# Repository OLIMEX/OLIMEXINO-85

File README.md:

This is the official repository for a number of OLIMEXINO-85 boards, manufactured by Olimex.

OLIMEXINO-85 boards are very tiny Arduino-like boards. They have functionality similar to Digistump's Digispark and Adafruit’s Trinket. The ATtiny85 microcontroller of each board comes preprogrammed with "Micronucleus" bootloater. This bootloader allows you to upload new software to the board via a personal computer and a USB cable. The boards work with the same Arduino distribution as Digispark.

In this repository you would find files suitable for the following boards:  

* OLIMEXINO-85-ASM: https://www.olimex.com/Products/Duino/AVR/OLIMEXINO-85-ASM/open-source-hardware
* OLIMEXINO-85-KIT: https://www.olimex.com/Products/Soldering-Kits/OLIMEXINO-85-KIT/open-source-hardware
* OLIMEXINO-85BC: https://www.olimex.com/Products/Duino/AVR/OLIMEXINO-85BC/open-source-hardware
* OLIMEXINO-85S: https://www.olimex.com/Products/Duino/AVR/OLIMEXINO-85S/open-source-hardware
* FOSDEM-85: https://www.olimex.com/Products/Soldering-Kits/FOSDEM-85/open-source-hardware

The SIMON-85 and SIMON-85-KIT boards have own repository available here: https://github.com/OLIMEX/SIMON-85

This repository contains a number of software files - firmware binaries, Arduino libraries, and ready-to-use examples. Note that the software files for the mentioned boards are the same for all boards in this repository. However, the hardware source files and pdfs for the above-mentioned boards are not the same.

##LICENSE
* Software License is GPL3
* Hardware License is Apache 2.0
* Documentation License is CC-BY-SA3.0 (https://creativecommons.org/licenses/by-sa/3.0/)

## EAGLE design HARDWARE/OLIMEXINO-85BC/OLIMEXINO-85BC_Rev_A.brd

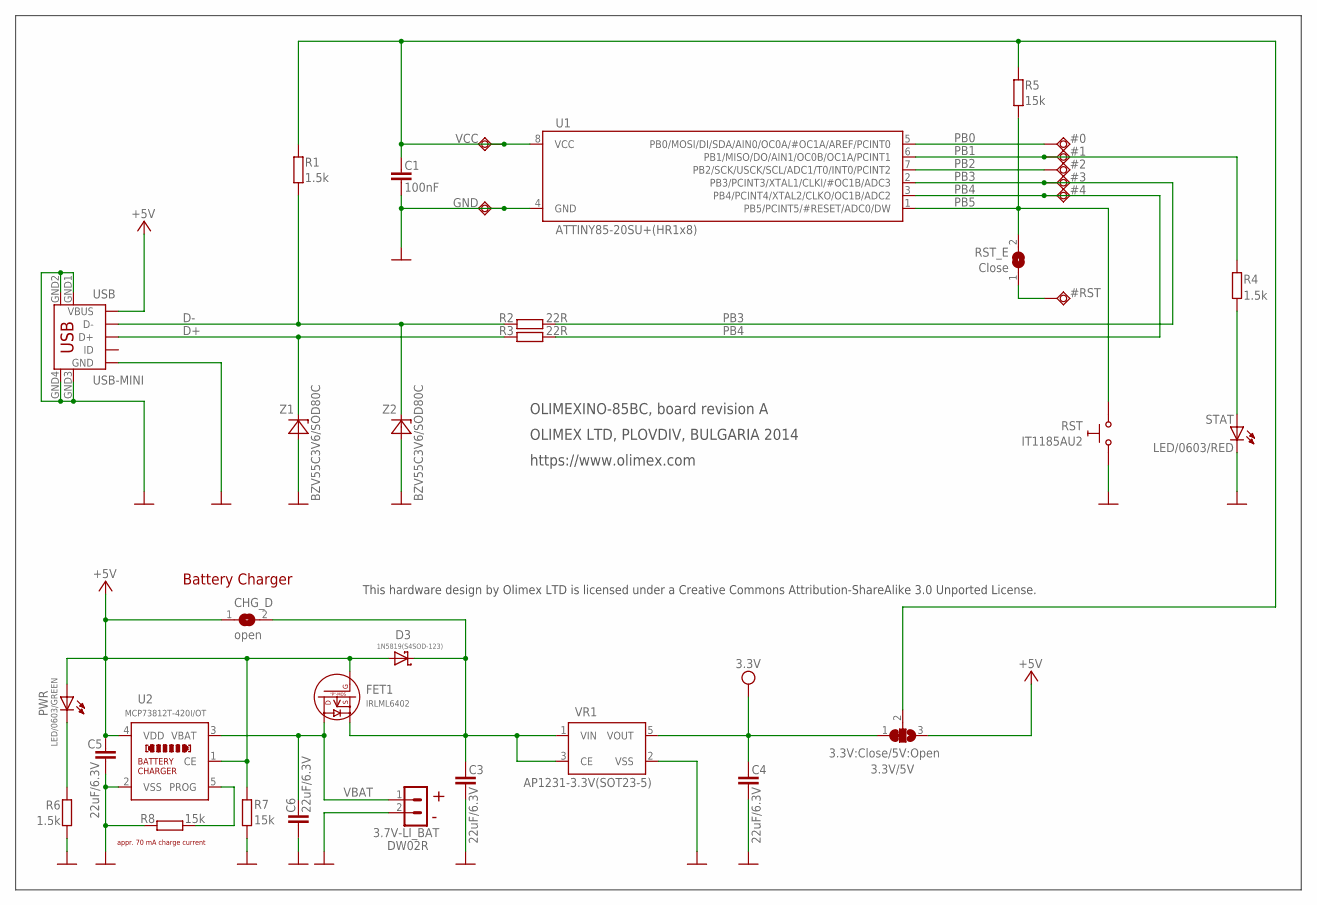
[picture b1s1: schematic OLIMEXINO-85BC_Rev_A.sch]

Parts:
3.3V/5V: 3.3V:Close/5V:Open; SJ_2_SMALL
3.7V-LI_BAT: DW02R
#0, #1, #2, #3, #4: TESTPAD3; TEST_PAD40/70/SQUARE
#RST: TESTPAD3; TEST_PAD40/70/SQUARE
C1: 100nF; C0603_DWS
C3, C4, C5, C6: 22uF/6.3V; C0603_DWS
CHG_D: open; SJ_1_SMALLER
D3: 1N5819(S4SOD-123); SOD-123
FET1: IRLML6402; SOT23
GND: TESTPAD3; TEST_PAD40/70/SQUARE
PWR: LED/0603/GREEN; LED-0603
R1, R4, R6: 1.5k; R0603_5MIL_DWS
R2, R3: 22R; R0603_5MIL_DWS
R5, R7, R8: 15k; R0603_5MIL_DWS
RST: IT1185AU2
RST_E: Close; SJ_1_SMALLER
STAT: LED/0603/RED; LED-0603
U1: ATTINY85-20SU+(HR1x8); SO-8
U2: MCP73812T-420I/OT; SOT-23-5
USB: USB-MINI; USB_MINI_9PIN
VCC: TESTPAD3; TEST_PAD40/70/SQUARE
VR1: AP1231-3.3V(SOT23-5); SOT-23-5
Z1, Z2: BZV55C3V6/SOD80C; MINI-MELF

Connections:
+5V: 3.3V/5V.3, C5.1, CHG_D.1, D3.A, FET1.1 (G), PWR.A, R7.1, U2.1 (CE), U2.4 (VDD), USB.VBUS
D+: R3.1, USB.D+, Z1.1 (C)
D-: R1.1, R2.1, USB.D-, Z2.1 (C)
GND: 3.7V-LI_BAT.2, C1.2, C3.2, C4.2, C5.2, C6.2, GND.P$1, R6.2, R7.2, R8.1, RST.2 (1), STAT.C, U1.4 (GND), U2.2 (VSS), USB.GND, USB.GND1, USB.GND2, USB.GND3, USB.GND4, VR1.2 (VSS), Z1.2 (A), Z2.2 (A)
MCU_VCC: 3.3V/5V.2, C1.1, R1.2, R5.2, U1.8 (VCC), VCC.P$1
unnamed: #RST.P$1, RST_E.1
unnamed: R4.1, STAT.A
unnamed: PWR.C, R6.1
unnamed: R8.2, U2.5 (PROG)
PB0: #0.P$1, U1.5 (PB0/MOSI/DI/SDA/AIN0/OC0A/#OC1A/AREF/PC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)
PB1: #1.P$1, R4.2, U1.6 (PB1/MISO/DO/AIN1/OC0B/OC1A/PCINT1)
PB2: #2.P$1, U1.7 (PB2/SCK/USCK/SCL/ADC1/T0/INT0/PCINT2)
PB3: #3.P$1, R2.2, U1.2 (PB3/PCINT3/XTAL1/CLKI/#OC1B/ADC3)
PB4: #4.P$1, R3.2, U1.3 (PB4/PCINT4/XTAL2/CLKO/OC1B/ADC2)
PB5: R5.1, RST.1 (0), RST_E.2, U1.1 (PB5/PCINT5/#RESET/ADC0/DW)
VBAT: 3.7V-LI_BAT.1, C6.1, FET1.3 (D), U2.3 (VBAT)
VCC: 3.3V/5V.1, C4.1, VR1.5 (VOUT)
VIN: C3.1, CHG_D.2, D3.C, FET1.2 (S), VR1.1 (VIN), VR1.3 (CE)

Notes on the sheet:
Battery Charger
appr. 70 mA charge current
OLIMEXINO-85BC, board revision A
OLIMEX LTD, PLOVDIV, BULGARIA 2014
https://www.olimex.com
This hardware design by Olimex LTD is licensed under a Creative Commons Attribution-ShareAlike 3.0 Unported License.

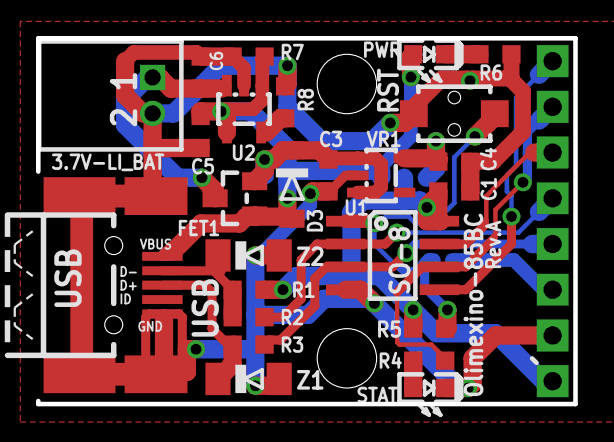
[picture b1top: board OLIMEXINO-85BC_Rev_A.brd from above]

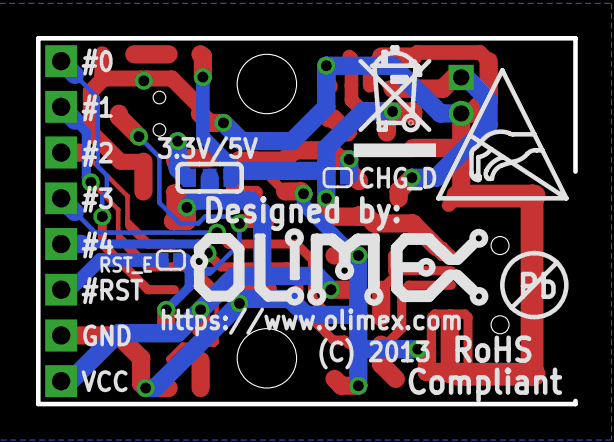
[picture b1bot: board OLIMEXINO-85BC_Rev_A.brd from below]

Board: 2 copper layers, 29.8 x 20.3 mm, 40 parts (7 on the bottom side), 18 nets.

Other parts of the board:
U$1: RECYCLE_BIN1/8
U$2: OLIMEX1_V
U$3: ESD_SYMBOL
U$4: PB_SMALL

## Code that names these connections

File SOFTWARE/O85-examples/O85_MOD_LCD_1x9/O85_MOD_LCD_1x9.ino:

/**********************************************************************************/
/*    Demo Program for:          						  */
/*	  Board: Olimexino-85                 					  */
/*    Manufacture: OLIMEX                                                   	  */
/*	  COPYRIGHT (C) 2014							  */
/*    Designed by:  Penko T. Bozhkov                                              */
/*    Revision       :  1.0.0 (initial)                                           */
/*    Date           :  03.02.2014                                                */
/*   Built with Arduino C/C++ Compiler, version: 1.0.4                            */
/**********************************************************************************/
// Very important!!!!! Change the I2C buffer size from 16 to 30!!!!!!!!!!!!!!!!!!!!
// Goto Digispark-Arduino-1.0.4\libraries\TinyWireM_Digispark\TinyWire.h and chage:
// #define USI_BUF_SIZE    30              // bytes in message buffer
// In other case, the demo will not work correctly
/*
  Action:
  =======
  Writes long string to the MOD-LCD-1x9 display.
  https://www.olimex.com/Products/Modules/LCD/MOD-LCD-1x9/open-source-hardware
  
  Notes: 
    1. Beware VCC not to exceed (3.6~3.8)V!!!!!
    2. Don't forget to connect external 2.2k Ohm pull-ups to the I2C line as shown below!
       This is vital as well!!!!!!!!!!!!!!!!!!!!!!!!!!!!!!!!!!!!!!!!!!!!!!!!!!!!!!!!!!!!!
 
  Simple Schematic:                    ------|2k2|----->VCC
  =================                   |    --|2k2|----->VCC
                                      |   |
  |---------------------------|       |   |       |----------------------|
  |                    |  #0  |-------|---o-------| UEXT<6>          | D |
  |                    |  #1  |       |           |                  | I |
  |                    |  #2  |-------o-----------| UEXT<5>          | S |
  |    OLIMEXINO-85    |  #3  |                   |                  | P |
  |                    |  #4  |                   |   MOD-LCD-1x9    | L |
  |                    | #RST |                   |                  | A |
  |                    | GND  |-------------------| UEXT<2>          | Y |
  |                    | VCC  |-------o-----------| UEXT<1>          |---|
  |---------------------------|       |           |----------------------|
                                      ----------------->VCC

  To upload to your Olimexino-85:
  1) Select the proper board from the Tools->Board Menu->Digispark 8mhz - NO USB(Tiny Core)
  2) Select Digispark from the Tools->Programmer
  3) Press the Upload button
  4) When you see the message: "Plug in device now... (will timeout in 60 seconds)", Plug in the Olimexino-85
*/
#include <USI_TWI_Master.h>
#include <TinyWireM.h>      // By default: SCL -> PB2(#2), SDA -> PB0(#0)
#include <avr/pgmspace.h>
#include <LCD1x9.h>
#include <inttypes.h>

#define LED1_PIN         1              // ATtiny85 Pin 6, PB1(#1)
#define LED2_PIN         4              // ATtiny85 Pin 3, PB4(#4)

char LongString[] PROGMEM = ("This is MOD-LCD-1x9 demo program. Hope you will enjoy this simple demo software! :-> ");
char TempValue[9] = {'#','I','N','I','T','I','A','L','#'};


/****************************************************/
/*  Function name: LCD_Write_LongString             */
/*  Parameters                                      */
/*    Input   :  *strp                              */
/*    Output  :  No                                 */
/*    Action: Writes the string to the LCD.         */
/****************************************************/
void LCD_Write_LongString(PGM_P strp){
  PGM_P tempp;
  
  tempp = strp;
  
  while(pgm_read_byte(strp)){
    for(unsigned char p=0; p<9; p++){
      TempValue[p] = pgm_read_byte(tempp);
      tempp++;
    }
    strp++;
    tempp = strp;
    lcd.write(TempValue);
    //delay(1000);
    Blink(LED1_PIN,2);
  }
  
  //Clear display
  lcd.write("         ");
  //delay(1000);
  Blink(LED1_PIN,2);
}


/****************************************************/
/*  Function name: Blink                            */
/*  Parameters                                      */
/*    Input   :  led, times                         */
/*    Output  :  No                                 */
/*    Action: Blinks the selected led.              */
/****************************************************/
void Blink(byte led, byte times){
  for (byte i=0; i<(times); i++){
    if(digitalRead(led)==LOW){
      digitalWrite(led,HIGH);
      delay (500);
    }
    else{
      digitalWrite(led,LOW);
      delay (100);
    }
  }
}


/****************************************************/
/*  Function name: setup                            */
/*  Parameters                                      */
/*    Input   :  No	                            */
/*    Output  :  No                                 */
/*    Action: Initializes all peripherals           */
/****************************************************/
void setup() {
  
  pinMode(LED1_PIN,OUTPUT);
  pinMode(LED2_PIN,OUTPUT);
  Blink(LED1_PIN,2);         // show it's alive
  
  TinyWireM.begin();         // I2C init
  lcd.init();
  
  digitalWrite(LED1_PIN,HIGH);
  digitalWrite(LED2_PIN,LOW);
  
  delay (100);
  lcd.write("*Welcome*");
  delay (1000);
}


/****************************************************/
/*  Function name: loop                             */
/*  Parameters                                      */
/*    Input   :  No	                            */
/*    Output  :  No                                 */
/*    Action: Reads and displays the temperature.   */
/****************************************************/ 
void loop() {
  
  // Display the string
  LCD_Write_LongString(LongString);
  
}
 
 
 

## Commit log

2015-07-06 85 boards update
2018-09-18 Updated
    BOMs and gerbers
2018-09-18 Create LICENSE
2025-12-04 Fix link to Arduino IDE configuration for DIGISPARK
    Updated the link for configuring Arduino IDE for DIGISPARK to an archived version.

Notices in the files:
HARDWARE/OLIMEXINO-85BC/OLIMEXINO-85BC_Rev_A.brd:
(C) 2013
